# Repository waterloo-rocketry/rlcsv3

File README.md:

# Remote Launch Control System

RLCS stands for Remote Launch Control System. It's purpose is to fill our rocket with ethanol and nitrous oxide, then ignite the ignition puck inside the rocket, all from a distance of 3000' away at launch control. To do so, it has control over multiple valves at the rocket, a linear actuator to disconnect the fill arm from the rocket, and 2 ignition coils inside the ignition puck.

### Repository Layout

All Arduino firmware code is in `/src`

All electrical schematics and PCB layouts are in `/schematics`

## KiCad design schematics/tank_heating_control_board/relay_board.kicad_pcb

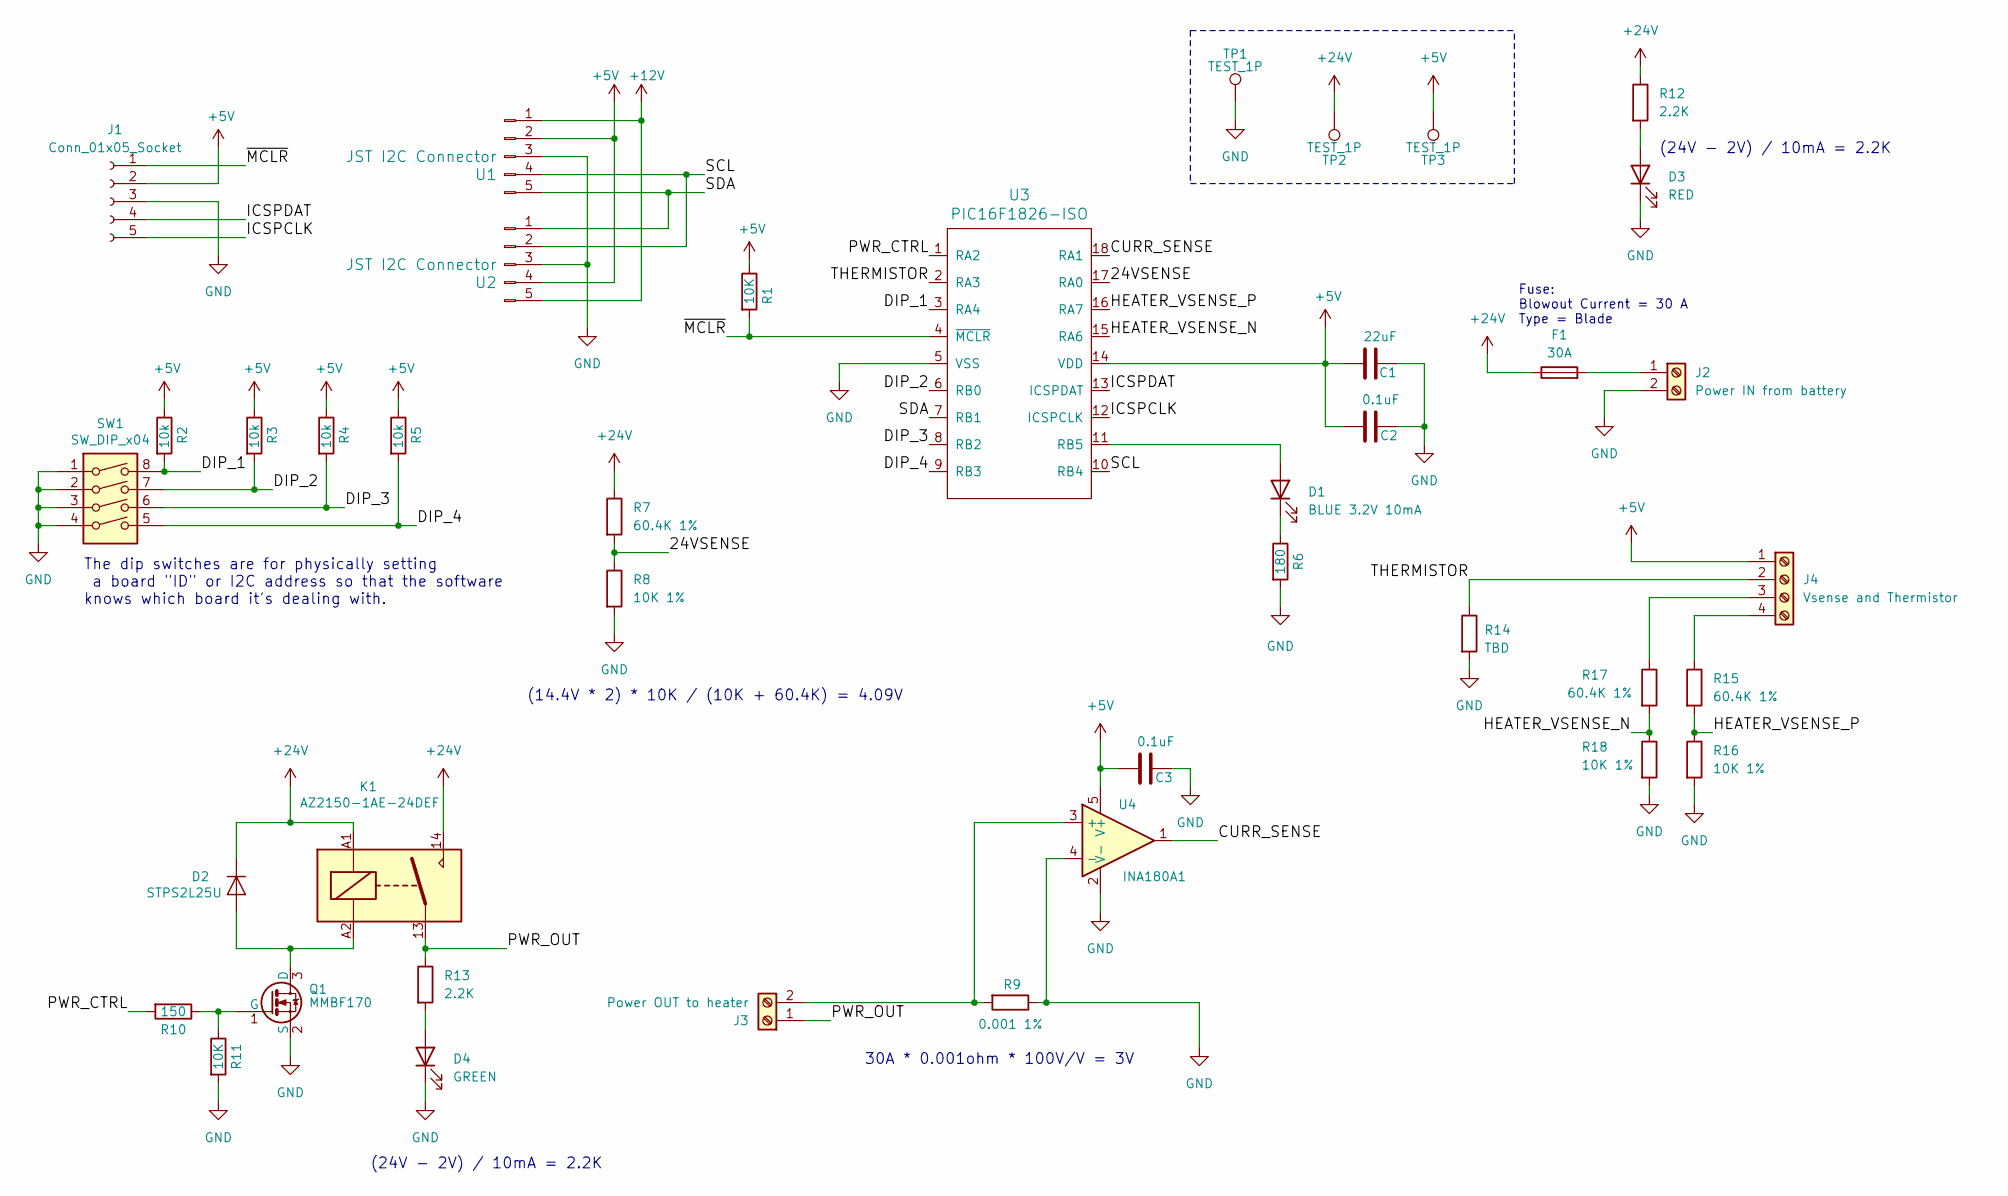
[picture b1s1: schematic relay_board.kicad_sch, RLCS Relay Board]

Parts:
C1: 22uF; C_0805_2012Metric_Pad1.18x1.45mm_HandSolder
C2, C3: 0.1uF; C_0805_2012Metric_Pad1.18x1.45mm_HandSolder
D1: BLUE 3.2V 10mA; LED_1206_3216Metric_Pad1.42x1.75mm_HandSolder
D2: STPS2L25U; D_SMB_Handsoldering
D3: RED; LED_1206_3216Metric_Pad1.42x1.75mm_HandSolder
D4: GREEN; LED_1206_3216Metric_Pad1.42x1.75mm_HandSolder
F1: 30A; 3557-10_KEY
J1: Conn_01x05_Socket; PinHeader_5x2.54_SMD_90deg_952-3198-1-ND
J2: Power IN from battery; CONN_1714955_PXC
J3: Power OUT to heater; CONN_1714955_PXC
J4: Vsense and Thermistor; TerminalBlock_Phoenix_PT-1,5-4-5.0-H_1x04_P5.00mm_Horizontal
K1: AZ2150-1AE-24DEF; AZ2150_AMZ
Q1: MMBF170; SOT-23
R1, R11: 10K; R_0805_2012Metric_Pad1.20x1.40mm_HandSolder
R2, R3, R4, R5: 10k; R_0805_2012Metric_Pad1.20x1.40mm_HandSolder
R6: 180; R_0805_2012Metric_Pad1.20x1.40mm_HandSolder
R7, R15, R17: 60.4K 1%; R_0805_2012Metric_Pad1.20x1.40mm_HandSolder
R8, R16, R18: 10K 1%; R_0805_2012Metric_Pad1.20x1.40mm_HandSolder
R9: 0.001 1%; R_2512_6332Metric_Pad1.40x3.35mm_HandSolder
R10: 150; R_0805_2012Metric_Pad1.20x1.40mm_HandSolder
R12, R13: 2.2K; R_0805_2012Metric_Pad1.20x1.40mm_HandSolder
R14: TBD; R_0805_2012Metric_Pad1.20x1.40mm_HandSolder
SW1: SW_DIP_x04; DIP_SWITCH_4X2
TP1, TP2, TP3: TEST_1P; Socket_Strip_Straight_1x01_Pitch2.54mm
U1, U2: JST I2C Connector; JST_XH_S5B-XH-A-1_1x05_P2.50mm_Horizontal
U3: PIC16F1826-ISO
U4: INA180A1; SOT-23-5_HandSoldering

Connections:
+5V: C1.1, C2.2, C3.2, J1.2, J4.1, R1.1, R2.1, R3.1, R4.1, R5.1, TP3.1, U1.2, U2.4, U3.14 (VDD), U4.5 (V+)
+12V: U1.1, U2.5
+24V: D2.1 (K), F1.1, K1.14, K1.A1, R7.1, R12.1, TP2.1
/24VSENSE: R7.2, R8.1, U3.17 (RA0)
/CURR_SENSE: U3.18 (RA1), U4.1
/DIP_1: R2.2, SW1.8, U3.3 (RA4)
/DIP_2: R3.2, SW1.7, U3.6 (RB0)
/DIP_3: R4.2, SW1.6, U3.8 (RB2)
/DIP_4: R5.2, SW1.5, U3.9 (RB3)
/HEATER_VSENSE_N: R17.2, R18.1, U3.15 (RA6)
/HEATER_VSENSE_P: R15.2, R16.1, U3.16 (RA7)
/ICSPCLK: J1.5, U3.12 (ICSPCLK)
/ICSPDAT: J1.4, U3.13 (ICSPDAT)
/PWR_CTRL: R10.2, U3.1 (RA2)
/PWR_OUT: J3.1, K1.13, R13.1
/SCL: U1.4, U2.2, U3.10 (RB4)
/SDA: U1.5, U2.1, U3.7 (RB1)
/THERMISTOR: J4.2, R14.1, U3.2 (RA3)
/~MCLR: J1.1, R1.2, U3.4 (~MCLR)
GND: C1.2, C2.1, C3.1, D3.1 (K), D4.1 (K), J1.3, J2.2, Q1.2 (S), R6.2, R8.2, R9.1, R11.2, R14.2, R16.2, R18.2, SW1.1, SW1.2, SW1.3, SW1.4, TP1.1, U1.3, U2.3, U3.5 (VSS), U4.2 (V-), U4.4 (-)
unnamed: D1.2 (A), U3.11 (RB5)
unnamed: D1.1 (K), R6.1
unnamed: D2.2 (A), K1.A2, Q1.3 (D)
unnamed: D3.2 (A), R12.2
unnamed: D4.2 (A), R13.2
unnamed: F1.2, J2.1
unnamed: J3.2, R9.2, U4.3 (+)
unnamed: J4.3, R17.1
unnamed: J4.4, R15.1
unnamed: Q1.1 (G), R10.1, R11.1

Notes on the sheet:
(14.4V * 2) * 10K / (10K + 60.4K) = 4.09V
(24V - 2V) / 10mA = 2.2K
Fuse: Blowout Current = 30 A Type = Blade
30A * 0.001ohm * 100V/V = 3V
The dip switches are for physically setting a board "ID" or I2C address so that the software knows which board it's dealing with.

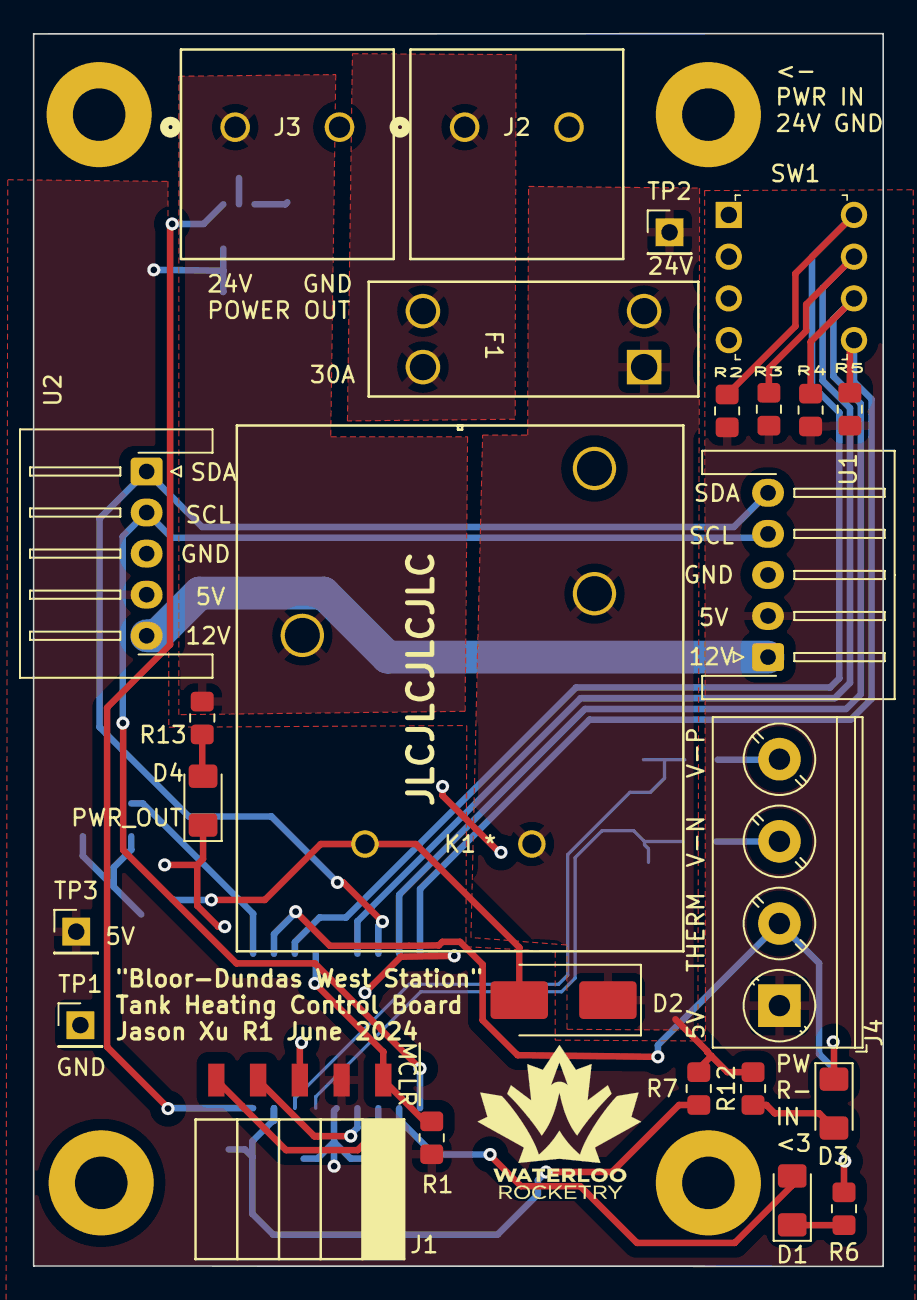
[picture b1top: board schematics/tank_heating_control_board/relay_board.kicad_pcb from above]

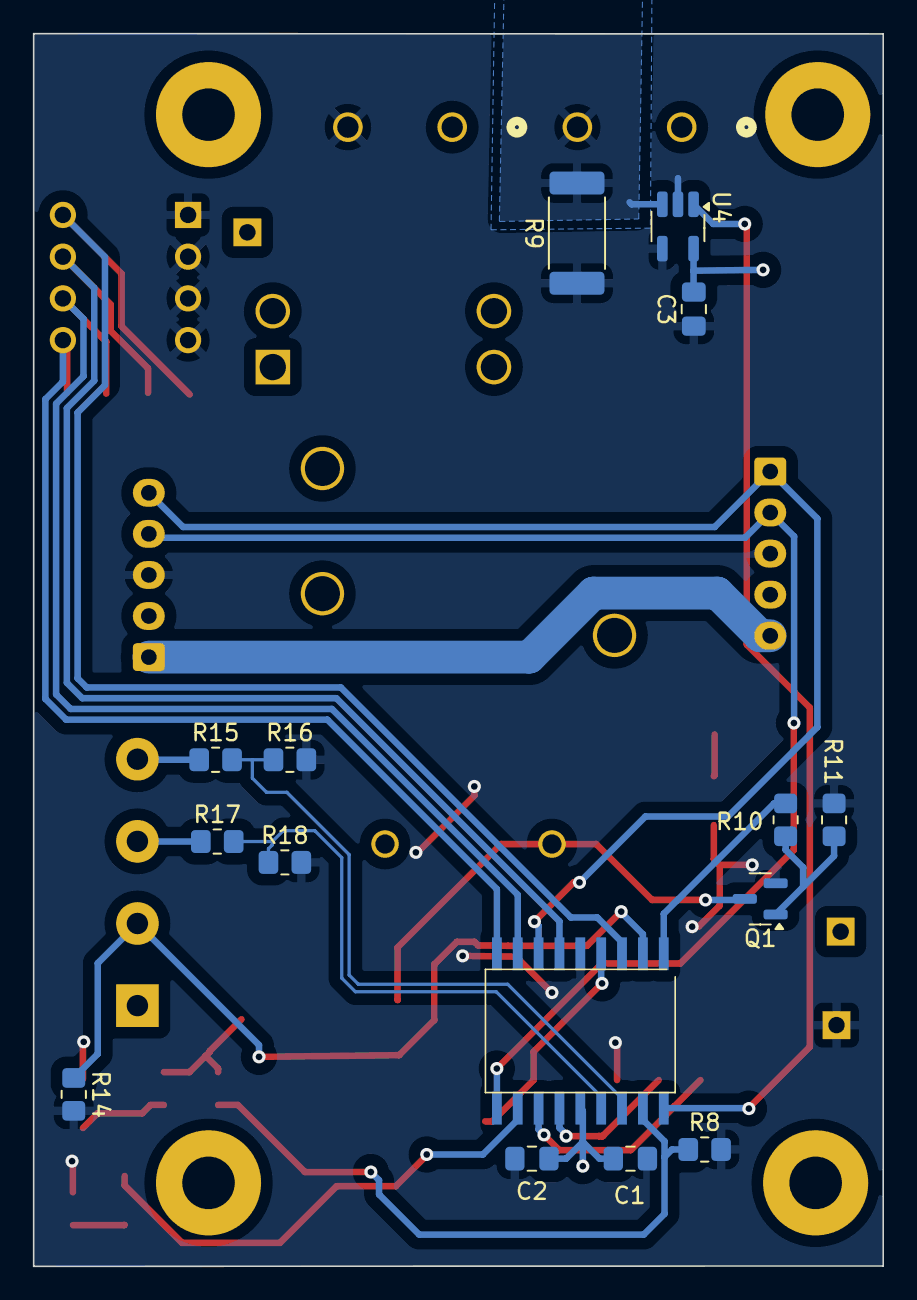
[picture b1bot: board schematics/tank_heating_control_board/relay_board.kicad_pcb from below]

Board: 2 copper layers, 51.7 x 75.0 mm, 40 parts (15 on the bottom side), 30 nets.

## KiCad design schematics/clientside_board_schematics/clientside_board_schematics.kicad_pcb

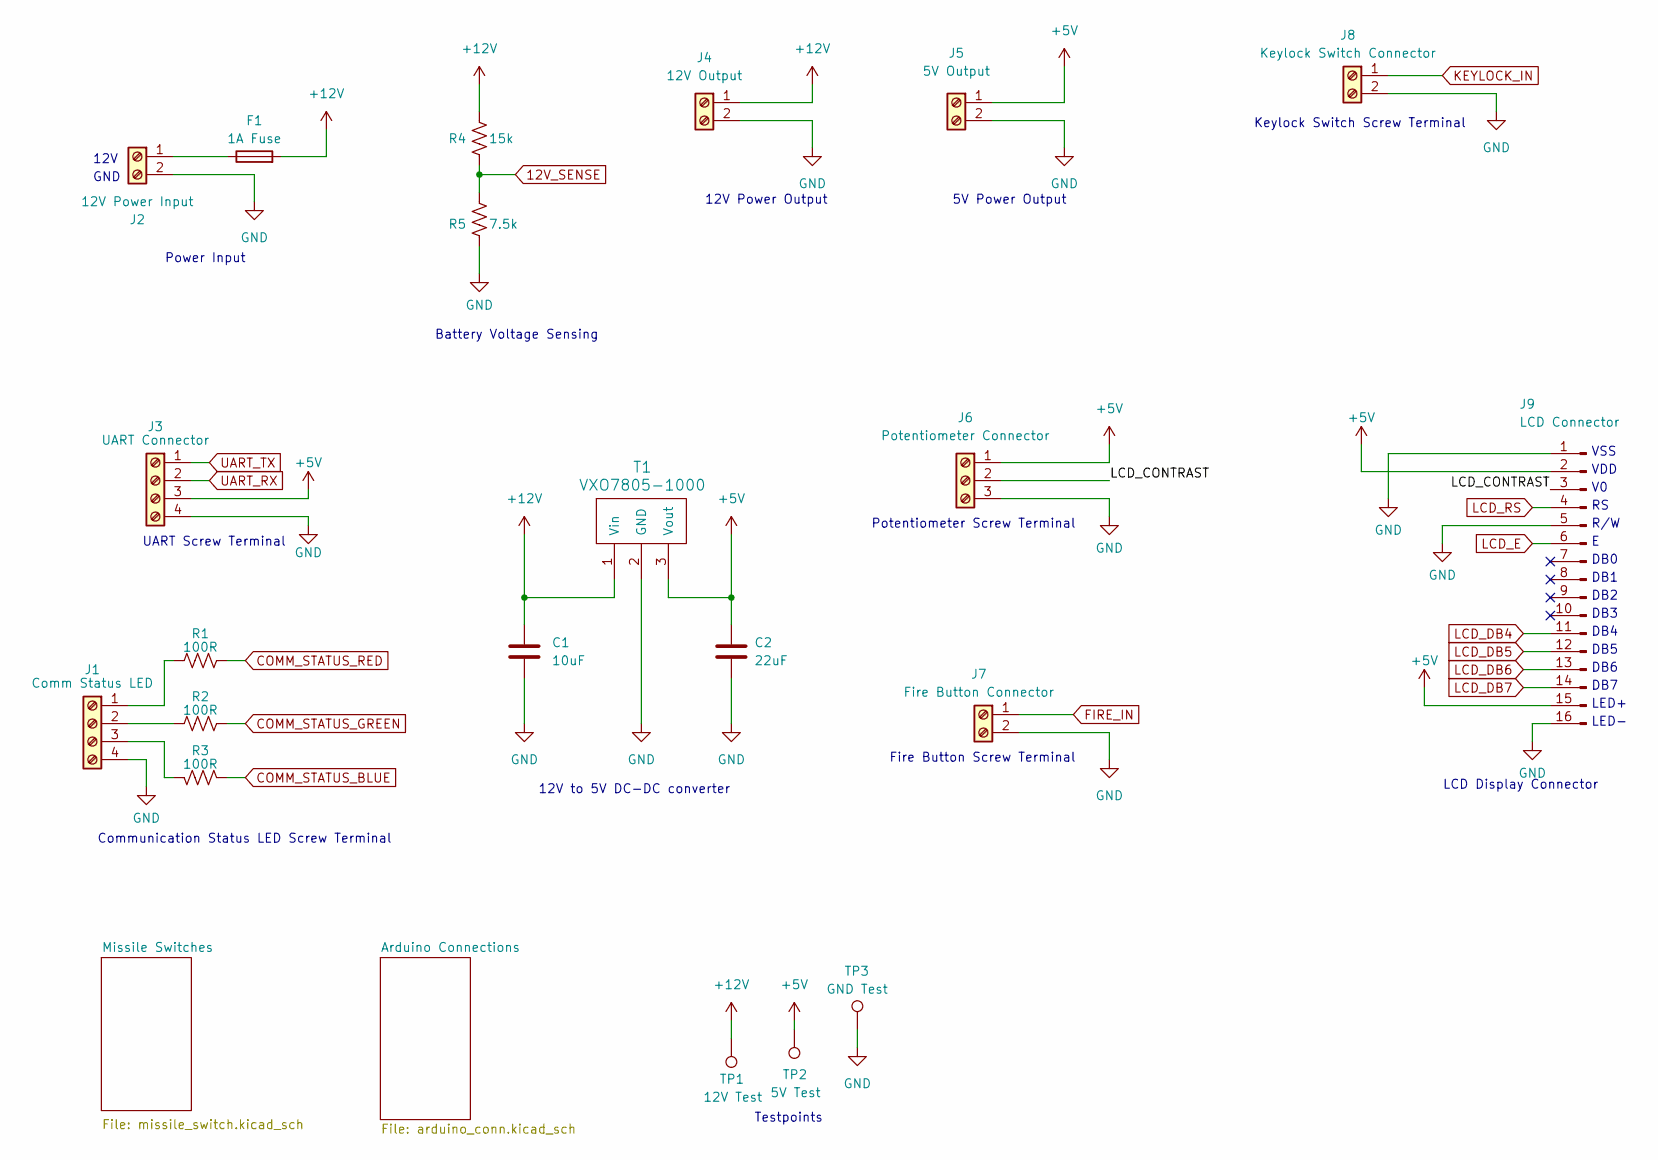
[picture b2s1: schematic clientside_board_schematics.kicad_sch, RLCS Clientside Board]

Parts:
C1: 10uF; C_0805_2012Metric_Pad1.18x1.45mm_HandSolder
C2: 22uF; C_0805_2012Metric_Pad1.18x1.45mm_HandSolder
F1: 1A Fuse; Fuseholder_Clip-5x20mm_Littelfuse_111_Inline_P20.00x5.00mm_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
J1: Comm Status LED; TerminalBlock_Phoenix_MKDS-1,5-4-5.08_1x04_P5.08mm_Horizont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
J2: 12V Power Input; TerminalBlock_Phoenix_MKDS-1,5-2-5.08_1x02_P5.08mm_Horizont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
J3: UART Connector; TerminalBlock_Phoenix_MKDS-1,5-4-5.08_1x04_P5.08mm_Horizont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
J4: 12V Output; TerminalBlock_Phoenix_MKDS-1,5-2-5.08_1x02_P5.08mm_Horizont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
J5: 5V Output; TerminalBlock_Phoenix_MKDS-1,5-2-5.08_1x02_P5.08mm_Horizont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
J6: Potentiometer Connector; TerminalBlock_Phoenix_MKDS-1,5-3-5.08_1x03_P5.08mm_Horizont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
J7: Fire Button Connector; TerminalBlock_Phoenix_MKDS-1,5-2-5.08_1x02_P5.08mm_Horizont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
J8: Keylock Switch Connector; TerminalBlock_Phoenix_MKDS-1,5-2-5.08_1x02_P5.08mm_Horizont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
J9: LCD Connector; NHD-0420DZ-FSW-FBW
R1, R2, R3: 100R; R_0805_2012Metric_Pad1.20x1.40mm_HandSolder
R4: 15k; R_0805_2012Metric_Pad1.20x1.40mm_HandSolder
R5: 7.5k; R_0805_2012Metric_Pad1.20x1.40mm_HandSolder
T1: VXO7805-1000; VXO78XX-1000
TP1: 12V Test; PinSocket_1x01_P2.00mm_Vertical
TP2: 5V Test; PinSocket_1x01_P2.00mm_Vertical
TP3: GND Test; PinSocket_1x01_P2.00mm_Vertical

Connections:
12V_SENSE: R4.2, R5.1; also elsewhere on the board
+5V: C2.1, J3.3, J5.1, J6.1, J9.2, J9.15, T1.3 (Vout), TP2.1; also elsewhere on the board
+12V: C1.1, F1.2, J4.1, R4.1, T1.1 (Vin), TP1.1
/LCD_CONTRAST: J6.2, J9.3
COMM_STATUS_BLUE: R3.2; also elsewhere on the board
COMM_STATUS_GREEN: R2.2; also elsewhere on the board
COMM_STATUS_RED: R1.2; also elsewhere on the board
FIRE_IN: J7.1; also elsewhere on the board
GND: C1.2, C2.2, J1.4, J2.2, J3.4, J4.2, J5.2, J6.3, J7.2, J8.2, J9.1, J9.5, J9.16, R5.2, T1.2 (GND), TP3.1; also elsewhere on the board
KEYLOCK_IN: J8.1; also elsewhere on the board
LCD_DB4: J9.11; also elsewhere on the board
LCD_DB5: J9.12; also elsewhere on the board
LCD_DB6: J9.13; also elsewhere on the board
LCD_DB7: J9.14; also elsewhere on the board
LCD_E: J9.6; also elsewhere on the board
LCD_RS: J9.4; also elsewhere on the board
unnamed: J1.1, R1.1
unnamed: J1.2, R2.1
unnamed: J1.3, R3.1
unnamed: F1.1, J2.1
UART_RX: J3.2; also elsewhere on the board
UART_TX: J3.1; also elsewhere on the board

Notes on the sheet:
LED-
Battery Voltage Sensing
DB0
R/W
DB2
5V Power Output
Keylock Switch Screw Terminal
DB6
GND
12V
LED+
12V Power Output
DB4
DB7
VSS
VDD
Potentiometer Screw Terminal
Testpoints
LCD Display Connector
DB3
Fire Button Screw Terminal
DB5
Power Input
DB1
UART Screw Terminal
12V to 5V DC-DC converter
Communication Status LED Screw Terminal

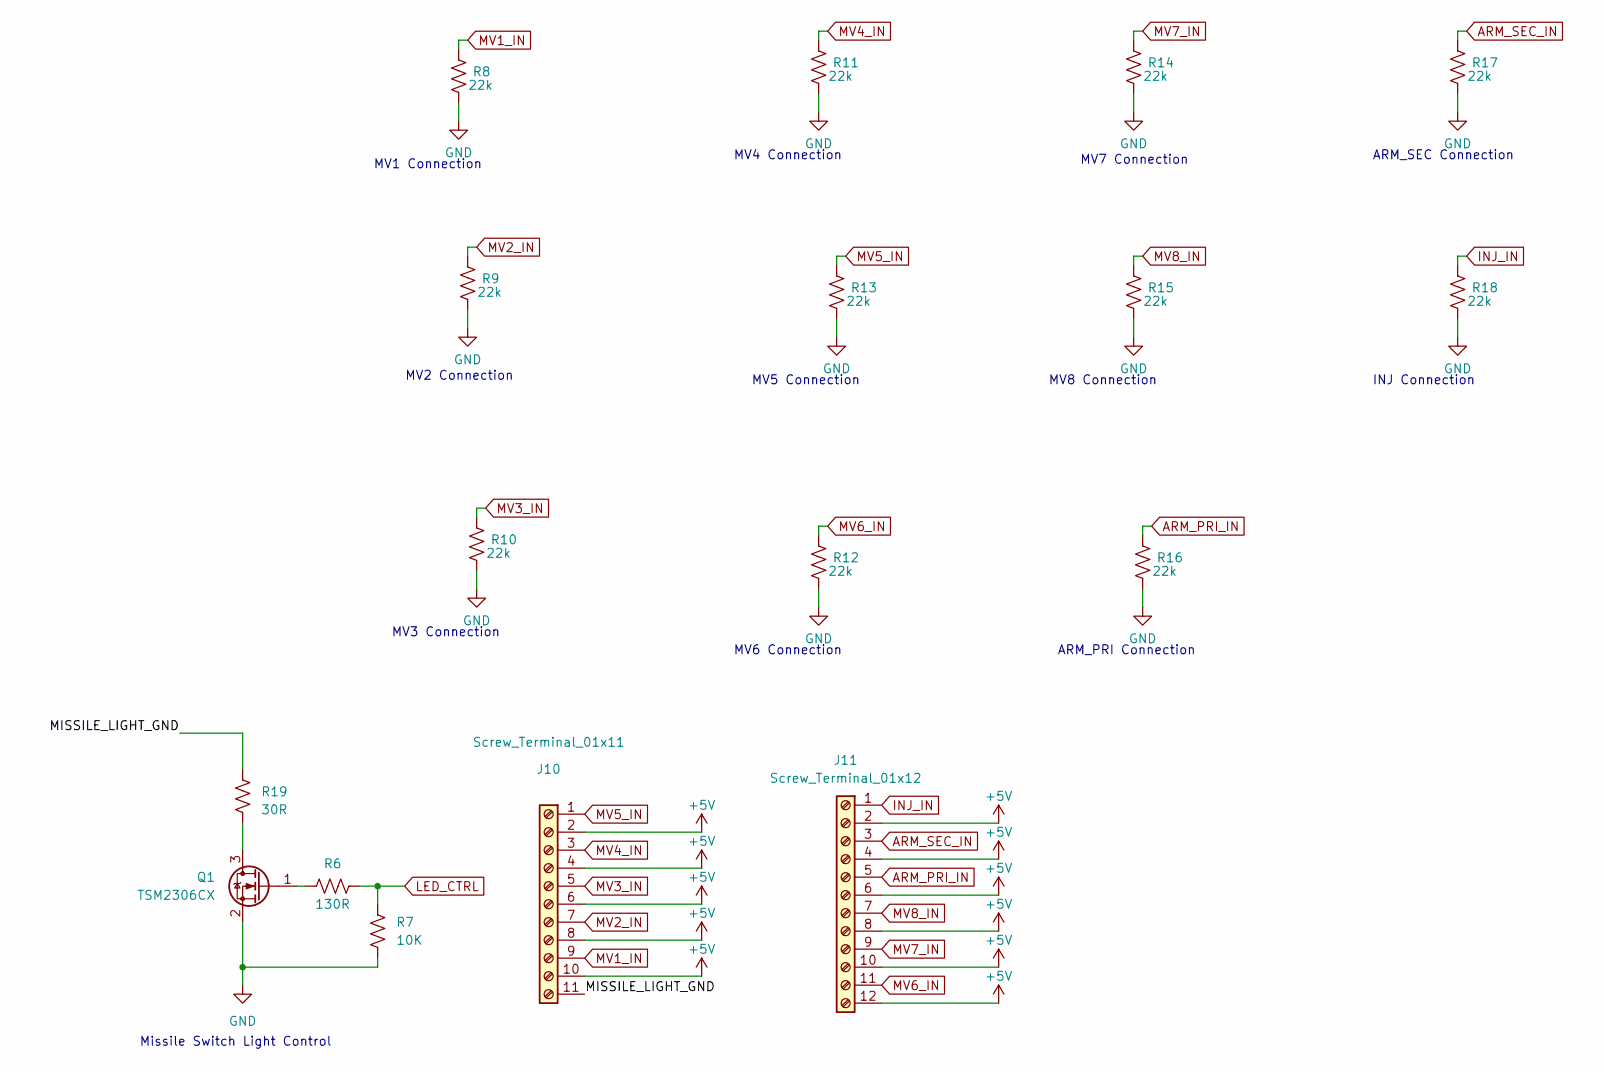
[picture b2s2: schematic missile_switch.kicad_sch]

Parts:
J10: Screw_Terminal_01x11; TerminalBlock_Phoenix_PT-1,5-11-3.5-H_1x11_P3.50mm_Horizont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
J11: Screw_Terminal_01x12; TerminalBlock_Phoenix_PT-1,5-12-3.5-H_1x12_P3.50mm_Horizont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
Q1: TSM2306CX; SOT-23_Handsoldering
R6: 130R; R_0805_2012Metric_Pad1.20x1.40mm_HandSolder
R7: 10K; R_0805_2012Metric_Pad1.20x1.40mm_HandSolder
R8, R9, R10, R11, R12, R13, R14, R15, R16, R17, R18: 22k; R_0805_2012Metric_Pad1.20x1.40mm_HandSolder
R19: 30R; R_0805_2012Metric_Pad1.20x1.40mm_HandSolder

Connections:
+5V: J10.2, J10.4, J10.6, J10.8, J10.10, J11.2, J11.4, J11.6, J11.8, J11.10, J11.12; also elsewhere on the board
/Missile Switches/MISSILE_LIGHT_GND: J10.11, R19.1
ARM_PRI_IN: J11.5, R16.1; also elsewhere on the board
ARM_SEC_IN: J11.3, R17.1; also elsewhere on the board
GND: Q1.2 (S), R7.2, R8.2, R9.2, R10.2, R11.2, R12.2, R13.2, R14.2, R15.2, R16.2, R17.2, R18.2; also elsewhere on the board
INJ_IN: J11.1, R18.1; also elsewhere on the board
LED_CTRL: R6.2, R7.1; also elsewhere on the board
MV1_IN: J10.9, R8.1; also elsewhere on the board
MV2_IN: J10.7, R9.1; also elsewhere on the board
MV3_IN: J10.5, R10.1; also elsewhere on the board
MV4_IN: J10.3, R11.1; also elsewhere on the board
MV5_IN: J10.1, R13.1; also elsewhere on the board
MV6_IN: J11.11, R12.1; also elsewhere on the board
MV7_IN: J11.9, R14.1; also elsewhere on the board
MV8_IN: J11.7, R15.1; also elsewhere on the board
unnamed: Q1.3 (D), R19.2
unnamed: Q1.1 (G), R6.1

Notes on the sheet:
MV8 Connection
MV3 Connection
ARM_SEC Connection
MV4 Connection
INJ Connection
MV6 Connection
MV1 Connection
MV5 Connection
MV7 Connection
ARM_PRI Connection
Missile Switch Light Control
MV2 Connection

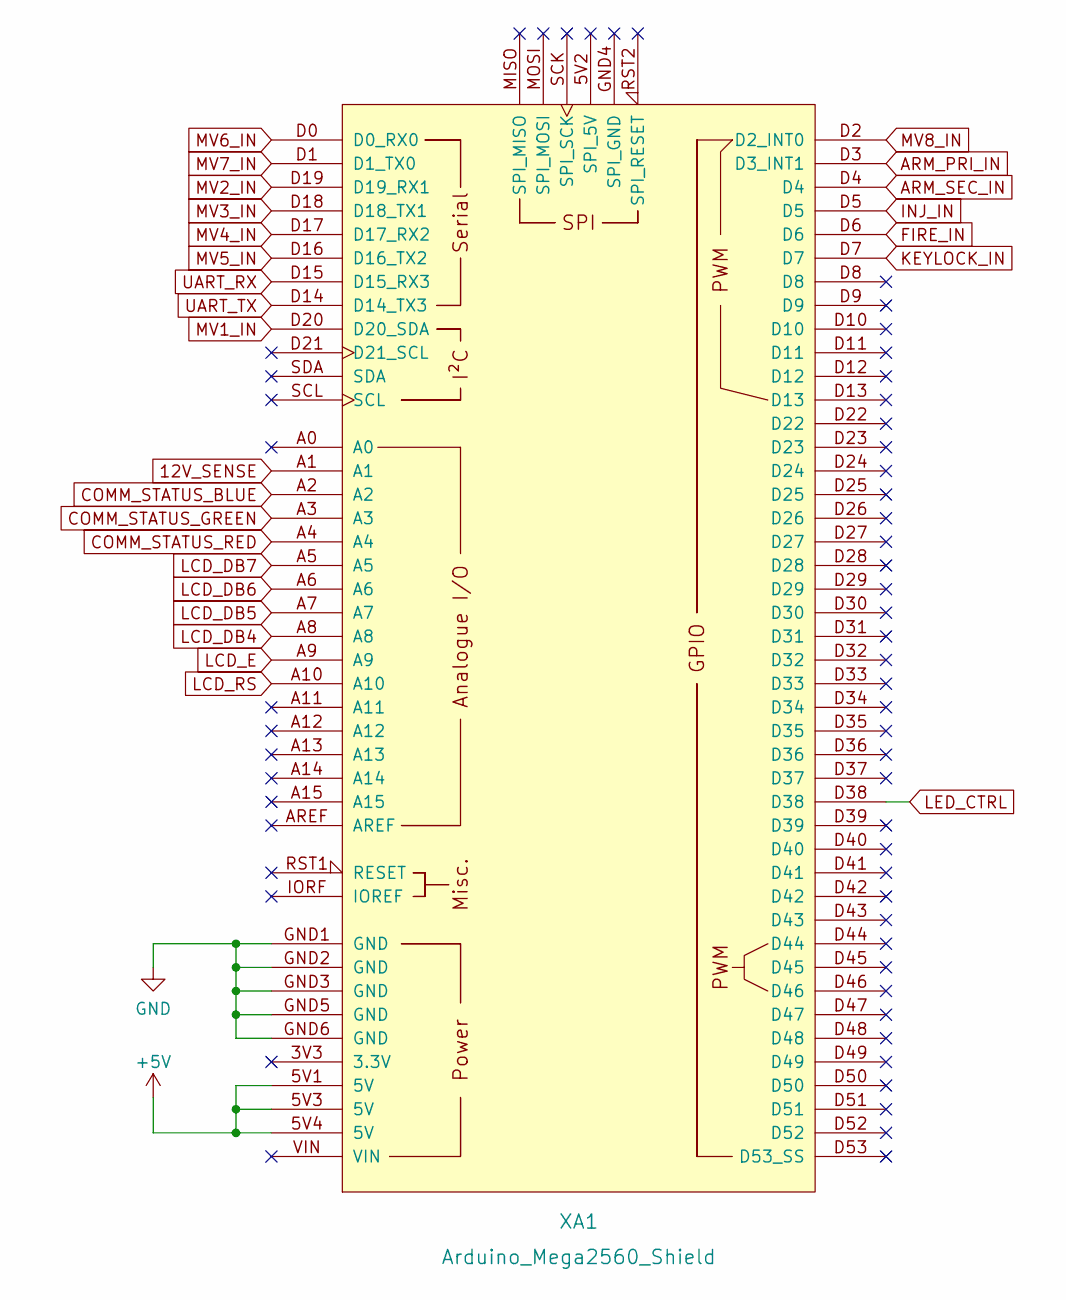
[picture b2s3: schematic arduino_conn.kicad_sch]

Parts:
XA1: Arduino_Mega2560_Shield

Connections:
12V_SENSE: XA1.A1; also elsewhere on the board
+5V: XA1.5V1 (5V), XA1.5V3 (5V), XA1.5V4 (5V); also elsewhere on the board
ARM_PRI_IN: XA1.D3 (D3_INT1); also elsewhere on the board
ARM_SEC_IN: XA1.D4; also elsewhere on the board
COMM_STATUS_BLUE: XA1.A2; also elsewhere on the board
COMM_STATUS_GREEN: XA1.A3; also elsewhere on the board
COMM_STATUS_RED: XA1.A4; also elsewhere on the board
FIRE_IN: XA1.D6; also elsewhere on the board
GND: XA1.GND1 (GND), XA1.GND2 (GND), XA1.GND3 (GND), XA1.GND5 (GND), XA1.GND6 (GND); also elsewhere on the board
INJ_IN: XA1.D5; also elsewhere on the board
KEYLOCK_IN: XA1.D7; also elsewhere on the board
LCD_DB4: XA1.A8; also elsewhere on the board
LCD_DB5: XA1.A7; also elsewhere on the board
LCD_DB6: XA1.A6; also elsewhere on the board
LCD_DB7: XA1.A5; also elsewhere on the board
LCD_E: XA1.A9; also elsewhere on the board
LCD_RS: XA1.A10; also elsewhere on the board
LED_CTRL: XA1.D38; also elsewhere on the board
MV1_IN: XA1.D20 (D20_SDA); also elsewhere on the board
MV2_IN: XA1.D19 (D19_RX1); also elsewhere on the board
MV3_IN: XA1.D18 (D18_TX1); also elsewhere on the board
MV4_IN: XA1.D17 (D17_RX2); also elsewhere on the board
MV5_IN: XA1.D16 (D16_TX2); also elsewhere on the board
MV6_IN: XA1.D0 (D0_RX0); also elsewhere on the board
MV7_IN: XA1.D1 (D1_TX0); also elsewhere on the board
MV8_IN: XA1.D2 (D2_INT0); also elsewhere on the board
UART_RX: XA1.D15 (D15_RX3); also elsewhere on the board
UART_TX: XA1.D14 (D14_TX3); also elsewhere on the board

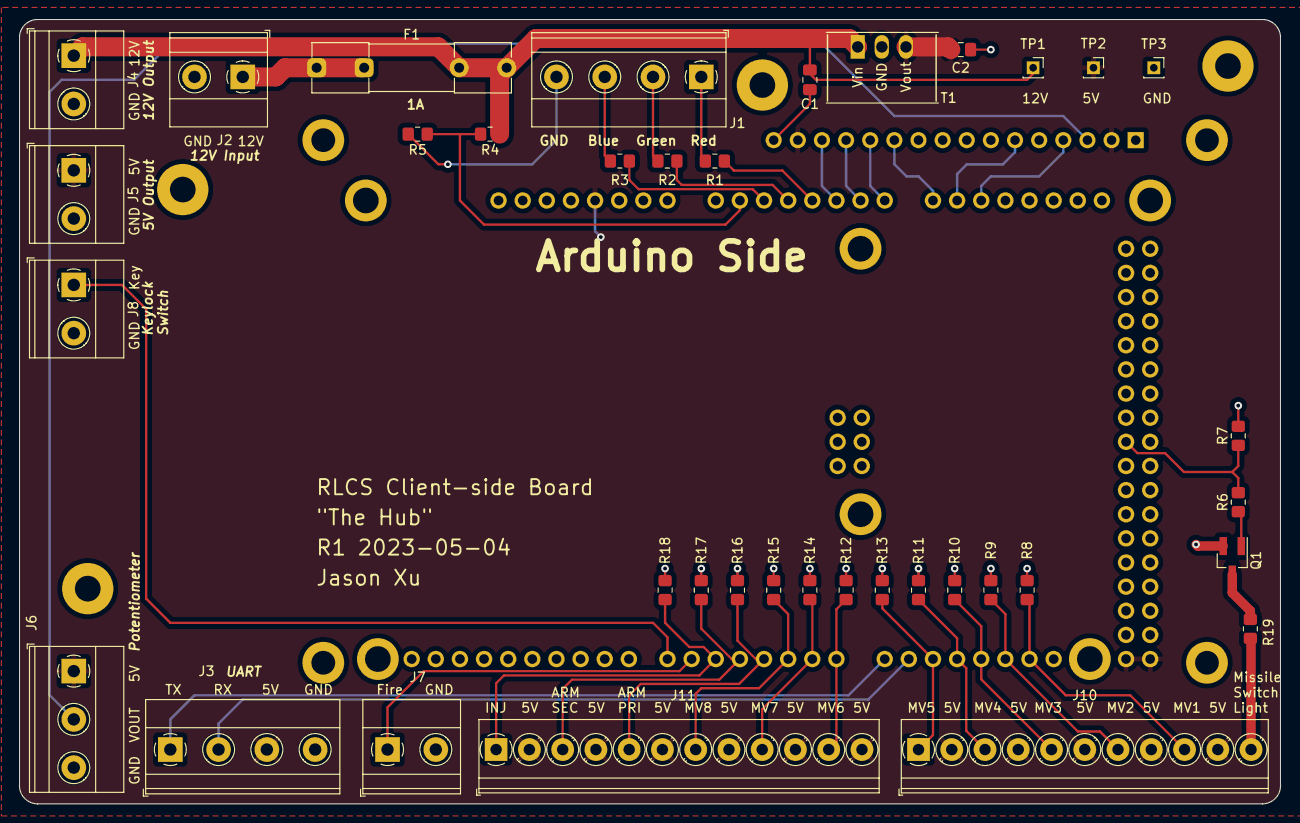
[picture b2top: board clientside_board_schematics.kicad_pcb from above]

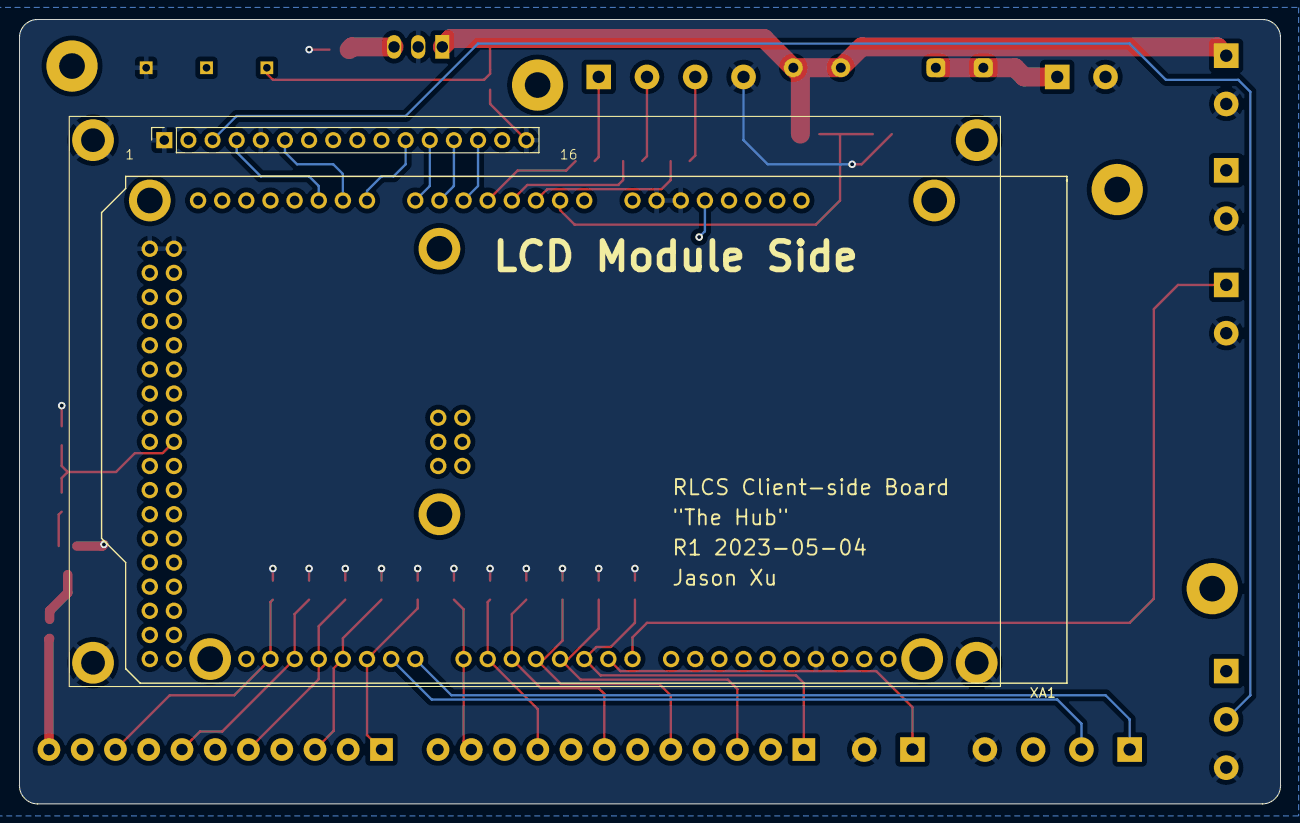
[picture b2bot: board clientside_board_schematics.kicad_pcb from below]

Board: 2 copper layers, 132.7 x 82.6 mm, 43 parts (2 on the bottom side), 37 nets.

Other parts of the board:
Left Mount: MountingHole_2.7mm_M2.5_Pad
Top Mount: MountingHole_2.7mm_M2.5_Pad
Top-Left Mount: MountingHole_2.7mm_M2.5_Pad
Top-Right Mount: MountingHole_2.7mm_M2.5_Pad

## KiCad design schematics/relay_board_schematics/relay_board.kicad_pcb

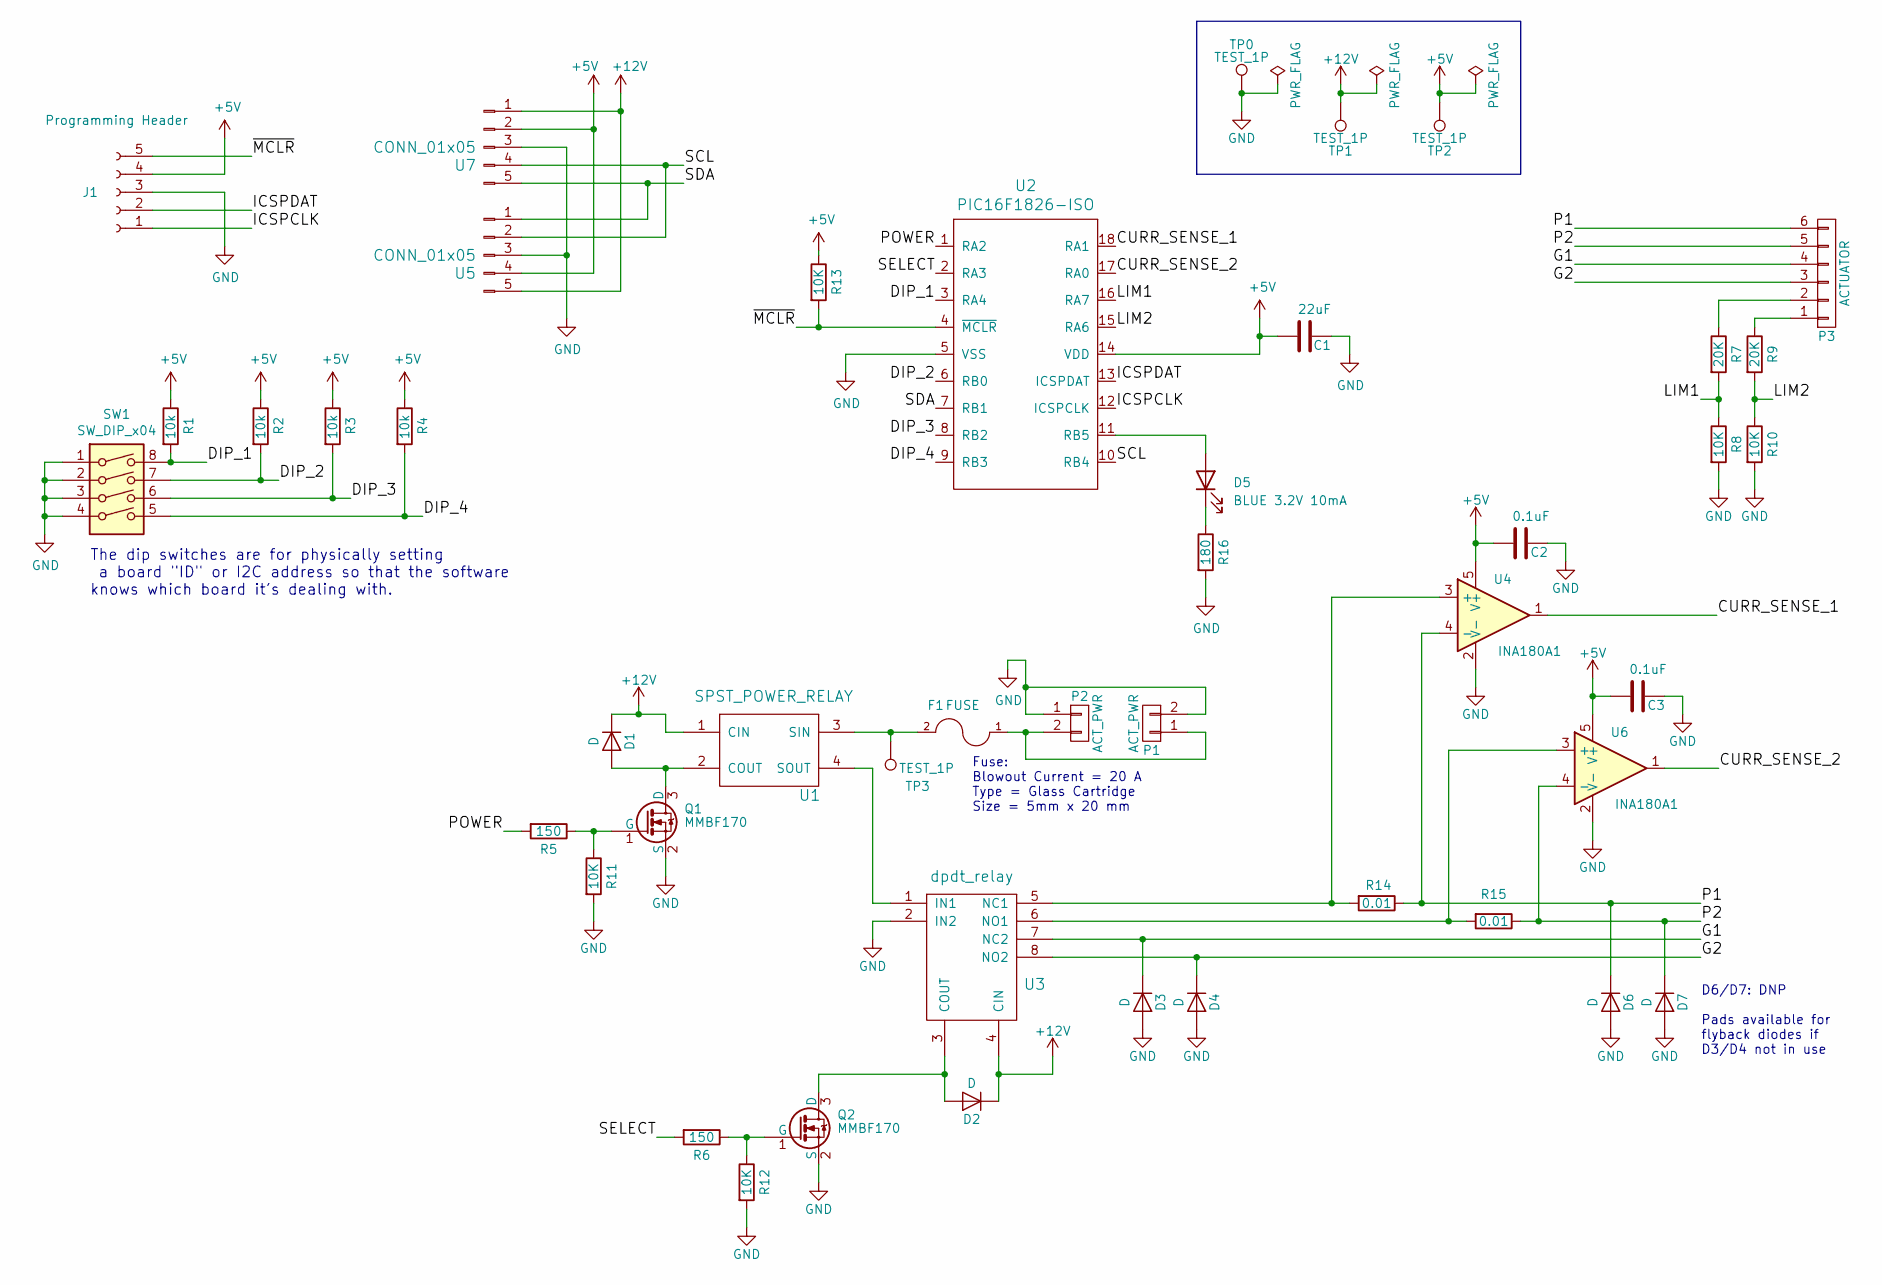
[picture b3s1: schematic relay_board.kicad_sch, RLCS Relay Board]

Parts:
C1: 22uF; C_0805_2012Metric_Pad1.18x1.45mm_HandSolder
C2, C3: 0.1uF; C_0805_2012Metric_Pad1.18x1.45mm_HandSolder
D1, D2, D3, D4, D6, D7: D; D_SMB_Handsoldering
D5: BLUE 3.2V 10mA; LED_1206_3216Metric_Pad1.42x1.75mm_HandSolder
F1: FUSE; littlefuse_01000020Z
J1: Programming Header; PinHeader_5x2.54_SMD_90deg_952-3198-1-ND
P1, P2: ACT_PWR; TerminalBlock_Phoenix_MKDS-1,5-2-5.08_1x02_P5.08mm_Horizont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
P3: ACTUATOR; TerminalBlock_Phoenix_MKDS-1,5-6_1x06_P5.00mm_Horizontal
Q1, Q2: MMBF170; SOT-23_Handsoldering
R1, R2, R3, R4: 10k; R_0805_2012Metric_Pad1.20x1.40mm_HandSolder
R5, R6: 150; R_0805_2012Metric_Pad1.20x1.40mm_HandSolder
R7, R9: 20K; R_0805_2012Metric_Pad1.20x1.40mm_HandSolder
R8, R10, R11, R12, R13: 10K; R_0805_2012Metric_Pad1.20x1.40mm_HandSolder
R14, R15: 0.01; R_2512_6332Metric_Pad1.40x3.35mm_HandSolder
R16: 180; R_0805_2012Metric_Pad1.20x1.40mm_HandSolder
SW1: SW_DIP_x04; DIP_SWITCH_4X2
TP0, TP1, TP2, TP3: TEST_1P; Socket_Strip_Straight_1x01_Pitch2.54mm
U1: SPST_POWER_RELAY; Relay_SPST_G5LE-1A
U2: PIC16F1826-ISO
U3: dpdt_relay; Relay_DPDT_RT424012F
U4, U6: INA180A1; SOT-23-5_HandSoldering
U5, U7: CONN_01x05; JST_XH_S5B-XH-A-1_1x05_P2.50mm_Horizontal

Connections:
+5V: C1.1, C2.2, C3.2, J1.4, R1.1, R2.1, R3.1, R4.1, R13.1, TP2.1, U2.14 (VDD), U4.5 (V+), U5.4, U6.5 (V+), U7.2; also elsewhere on the board
+12V: D1.1 (K), D2.1 (K), TP1.1, U1.1 (CIN), U3.4 (CIN), U5.5, U7.1
/CURR_SENSE_1: U2.18 (RA1), U4.1
/CURR_SENSE_2: U2.17 (RA0), U6.1
/DIP_1: R1.2, SW1.8, U2.3 (RA4)
/DIP_2: R2.2, SW1.7, U2.6 (RB0)
/DIP_3: R3.2, SW1.6, U2.8 (RB2)
/DIP_4: R4.2, SW1.5, U2.9 (RB3)
/G1: D3.1 (K), P3.4, U3.7 (NC2)
/G2: D4.1 (K), P3.3, U3.8 (NO2)
/ICSPCLK: J1.1, U2.12 (ICSPCLK)
/ICSPDAT: J1.2, U2.13 (ICSPDAT)
/LIM1: R7.2, R8.1, U2.16 (RA7)
/LIM2: R9.2, R10.1, U2.15 (RA6)
/P1: D6.1 (K), P3.6, R14.1, U4.4 (-)
/P2: D7.1 (K), P3.5, R15.1, U6.4 (-)
/POWER: R5.2, U2.1 (RA2)
/SCL: U2.10 (RB4), U5.2, U7.4
/SDA: U2.7 (RB1), U5.1, U7.5
/SELECT: R6.2, U2.2 (RA3)
/~MCLR: J1.5, R13.2, U2.4 (~MCLR)
GND: C1.2, C2.1, C3.1, D3.2 (A), D4.2 (A), D6.2 (A), D7.2 (A), J1.3, P1.2, P2.1, Q1.2 (S), Q2.2 (S), R8.2, R10.2, R11.2, R12.2, R16.2, SW1.1, SW1.2, SW1.3, SW1.4, TP0.1, U2.5 (VSS), U3.2 (IN2), U4.2 (V-), U5.3, U6.2 (V-), U7.3; also elsewhere on the board
unnamed: D1.2 (A), Q1.3 (D), U1.2 (COUT)
unnamed: D2.2 (A), Q2.3 (D), U3.3 (COUT)
unnamed: D5.1 (K), R16.1
unnamed: D5.2 (A), U2.11 (RB5)
unnamed: F1.1, P1.1, P2.2
unnamed: F1.2, TP3.1, U1.3 (SIN)
unnamed: P3.1, R9.1
unnamed: P3.2, R7.1
unnamed: Q1.1 (G), R5.1, R11.1
unnamed: Q2.1 (G), R6.1, R12.1
unnamed: R14.2, U3.5 (NC1), U4.3 (+)
unnamed: R15.2, U3.6 (NO1), U6.3 (+)
unnamed: U1.4 (SOUT), U3.1 (IN1)

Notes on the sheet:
D6/D7: DNP Pads available for flyback diodes if D3/D4 not in use
Fuse: Blowout Current = 20 A Type = Glass Cartridge Size = 5mm x 20 mm
The dip switches are for physically setting a board "ID" or I2C address so that the software knows which board it's dealing with.
